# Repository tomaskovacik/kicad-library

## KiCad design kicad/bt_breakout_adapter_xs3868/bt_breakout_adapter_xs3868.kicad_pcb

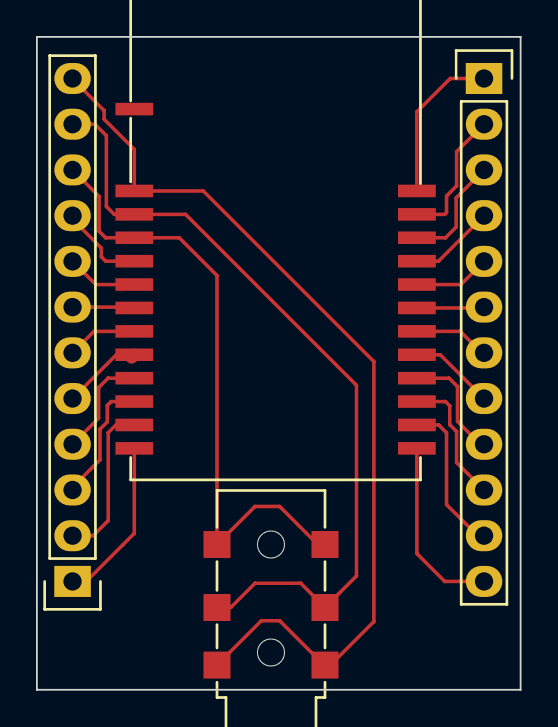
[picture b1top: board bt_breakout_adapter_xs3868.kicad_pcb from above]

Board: 2 copper layers, 26.9 x 36.3 mm, 4 parts (0 on the bottom side), 24 nets.

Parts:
J1: 3.5mm_stereo_jack_PJ242
P1, P2: CONN_01X12; Pin_Header_Straight_1x12
U1: XS3860; XS3868

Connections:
unnamed: J1.1, P1.12, U1.2
unnamed: J1.2, P1.11, U1.3
unnamed: J1.5, P1.10, U1.4
unnamed: P1.1, U1.13
unnamed: P1.2, U1.12
unnamed: P1.3, U1.11
unnamed: P1.4, U1.10
unnamed: P1.5, U1.9
unnamed: P1.6, U1.8
unnamed: P1.7, U1.7
unnamed: P1.8, U1.6
unnamed: P1.9, U1.5
unnamed: P2.1, U1.25
unnamed: P2.2, U1.24
unnamed: P2.3, U1.23
unnamed: P2.4, U1.22
unnamed: P2.5, U1.21
unnamed: P2.6, U1.20
unnamed: P2.7, U1.19
unnamed: P2.8, U1.18
unnamed: P2.9, U1.17
unnamed: P2.10, U1.16
unnamed: P2.11, U1.15
unnamed: P2.12, U1.14

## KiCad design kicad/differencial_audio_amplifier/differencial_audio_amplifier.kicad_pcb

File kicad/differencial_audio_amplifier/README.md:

diferential audio preamplifier for OVC3860 based bluetooth modules, with 0.9V on common audio output, works with blk-md-spk-b, XS3868 and S3860M-S and others.

you can buy boards on tindie:

https://www.tindie.com/products/tomaskovacik/pcb-for-diferential-audio-amplifier/

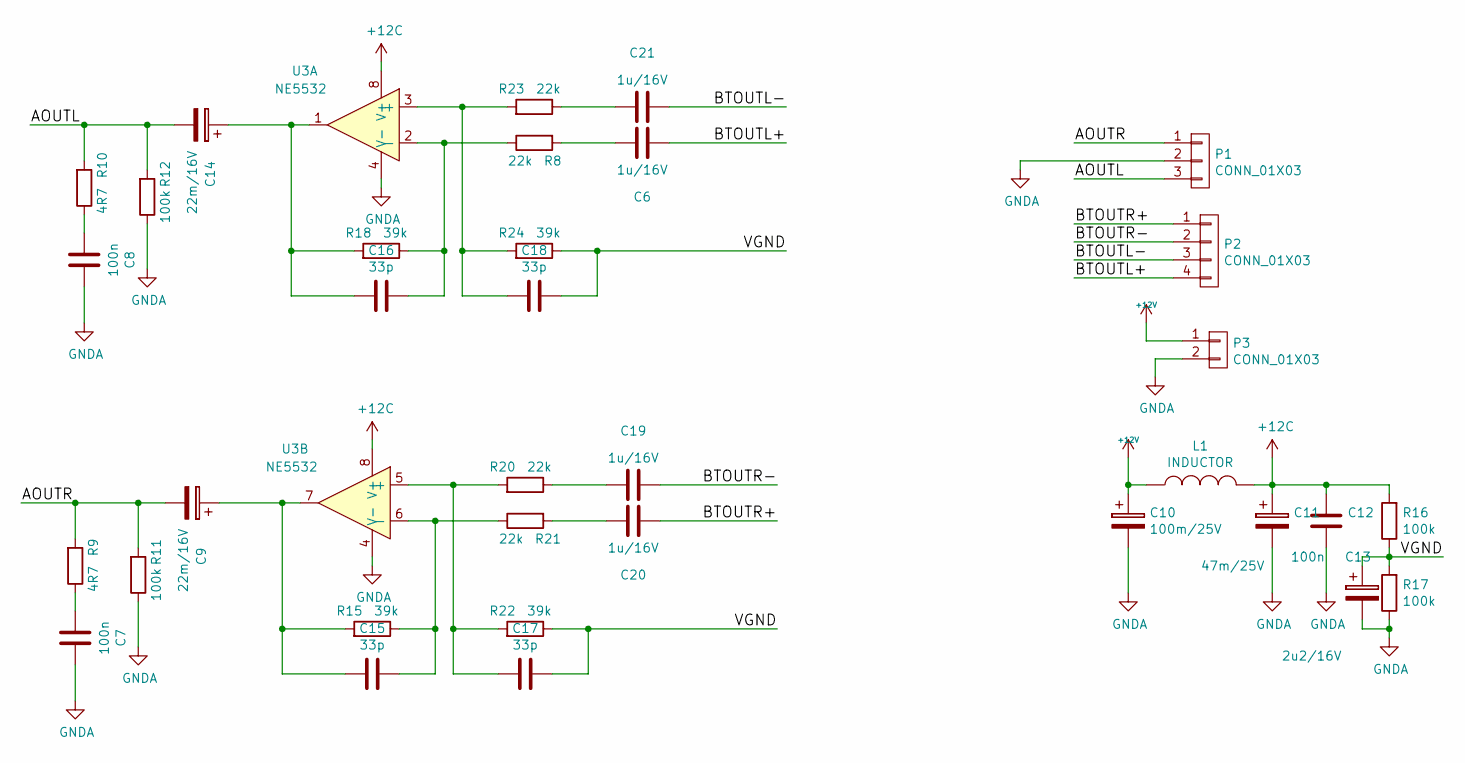
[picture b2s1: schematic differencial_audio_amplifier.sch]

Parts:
C6, C19, C20, C21: 1u/16V; C_0805_HandSoldering
C7, C8, C12: 100n; C_0805_HandSoldering
C9, C14: 22m/16V; c_elec_5x5.3
C10: 100m/25V; c_elec_6.3x7.7
C11: 47m/25V; TantalC_SizeD_EIA-7343_HandSoldering
C13: 2u2/16V; TantalC_SizeA_EIA-3216_HandSoldering
C15, C16, C17, C18: 33p; C_0805_HandSoldering
L1: INDUCTOR; SMD-1210_Pol
P1: CONN_01X03; Pin_Header_Straight_1x03
P2: CONN_01X03; Pin_Header_Straight_1x04
P3: CONN_01X03; Pin_Header_Straight_1x02
R8, R20, R21, R23: 22k; R_0805_HandSoldering
R9, R10: 4R7; R_0805_HandSoldering
R11, R12, R16, R17: 100k; R_0805_HandSoldering
R15, R18, R22, R24: 39k; R_0805_HandSoldering
U3: NE5532; SOIC-8-N

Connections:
+12C: C11.1, C12.1, L1.2, R16.2, U3.8 (V+)
+12V: C10.1, L1.1, P3.1
/AOUTL: C14.2, P1.3, R10.2, R12.2
/AOUTR: C9.2, P1.1, R9.2, R11.2
/BTOUTL+: C6.1, P2.4
/BTOUTL-: C21.2, P2.3
/BTOUTR+: C20.1, P2.1
/BTOUTR-: C19.2, P2.2
/VGND: C13.1, C17.2, C18.2, R16.1, R17.2, R22.1, R24.1
GNDA: C7.2, C8.2, C10.2, C11.2, C12.2, C13.2, P1.2, P3.2, R11.1, R12.1, R17.1, U3.4 (V-)
unnamed: C6.2, R8.2
unnamed: C7.1, R9.1
unnamed: C8.1, R10.1
unnamed: C14.1, C16.1, R18.2, U3.1
unnamed: C9.1, C15.1, R15.2, U3.7
unnamed: C15.2, R15.1, R21.1, U3.6 (-)
unnamed: C16.2, R8.1, R18.1, U3.2 (-)
unnamed: C17.1, R20.2, R22.2, U3.5 (+)
unnamed: C18.1, R23.2, R24.2, U3.3 (+)
unnamed: C19.1, R20.1
unnamed: C20.2, R21.2
unnamed: C21.1, R23.1

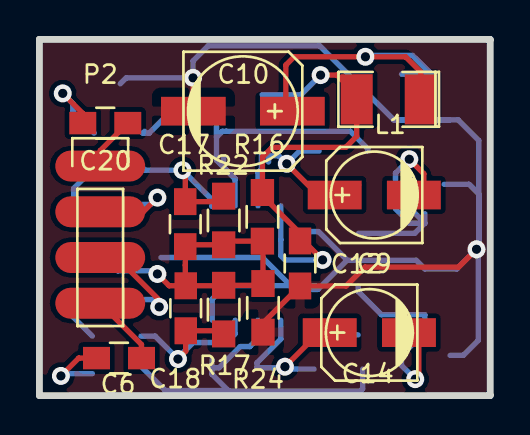
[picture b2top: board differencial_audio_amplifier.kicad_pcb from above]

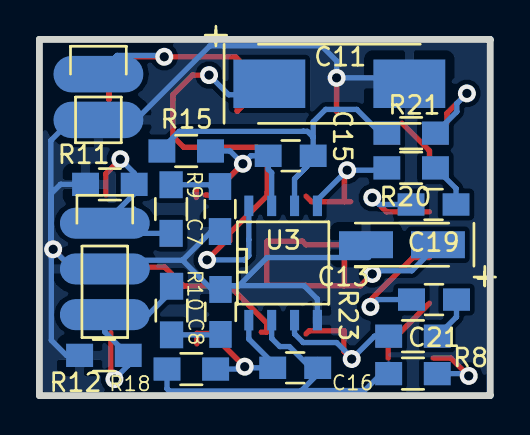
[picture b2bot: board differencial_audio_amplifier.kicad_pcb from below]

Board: 2 copper layers, 25.0 x 19.8 mm, 35 parts (21 on the bottom side), 22 nets.

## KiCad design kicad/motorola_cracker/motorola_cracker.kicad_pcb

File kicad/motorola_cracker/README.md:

for audi chorus1,concert1 cassete radios:

software: http://uloz.to/xmBngiSq/motcrack-v6-exe

to recover password,fix volume problem (yet untested!!!!) simple use dump 4321_no_password.e2p from dumps directory and rewrite MCU eeprom

blog post: http://kovo-blog.blogspot.sk/2015/08/audi-chorus-concert-how-to-recover.html

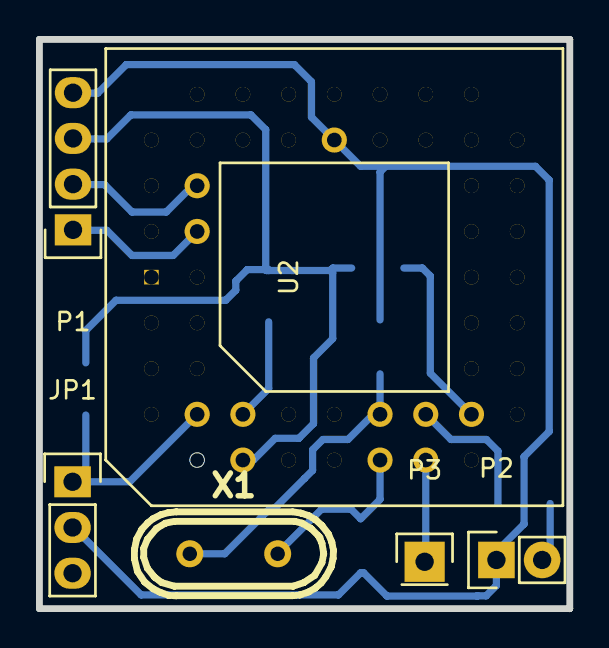
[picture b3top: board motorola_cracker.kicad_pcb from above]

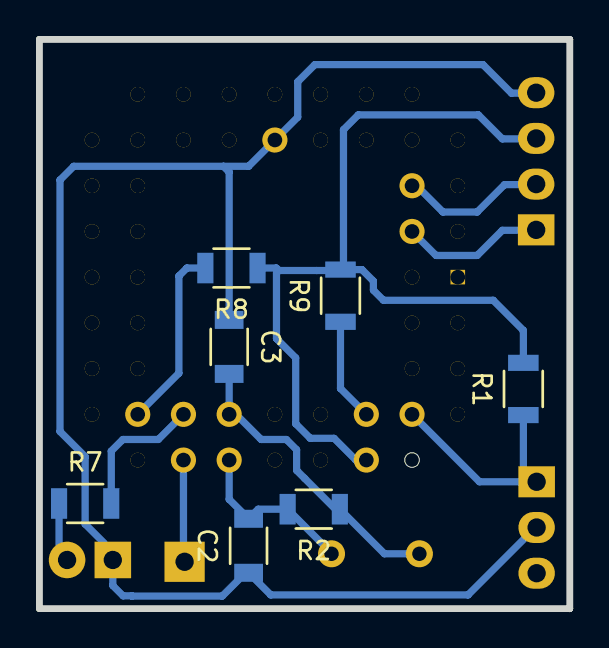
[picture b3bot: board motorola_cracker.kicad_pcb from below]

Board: 2 copper layers, 29.5 x 31.6 mm, 13 parts (7 on the bottom side), 12 nets.

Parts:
C2, C3: 22p; C_1206
JP1: JUMPER3; Pin_Header_Straight_1x03
P1: UART; Pin_Header_Straight_1x04
P2: +12V; Socket_Strip_Straight_1x02
P3: RTS; Pin_Header_Straight_1x01
R1, R7: 10k; R_1206
R2: 100M; R_1206
R8, R9: 1k; R_1206
U2: 68HC05_PLCC; PLCC52
X1: 4Mhz; Crystal_HC49-U_Vertical

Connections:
+5V: P1.3, R1.2, R8.1, R9.2, U2.10
/+12V: P2.2, R7.1
/RESET: P3.1, U2.18
/RX: P1.2, U2.50
/TX: P1.1, U2.52
GND: C2.1, C3.1, JP1.2, P1.4, P2.1, U2.41
unnamed: C2.2, R2.2, U2.16, X1.2
unnamed: C3.2, R2.1, U2.17, X1.1
unnamed: JP1.1, R1.1, U2.9
unnamed: R7.2, U2.19
unnamed: R8.2, U2.22
unnamed: R9.1, U2.11

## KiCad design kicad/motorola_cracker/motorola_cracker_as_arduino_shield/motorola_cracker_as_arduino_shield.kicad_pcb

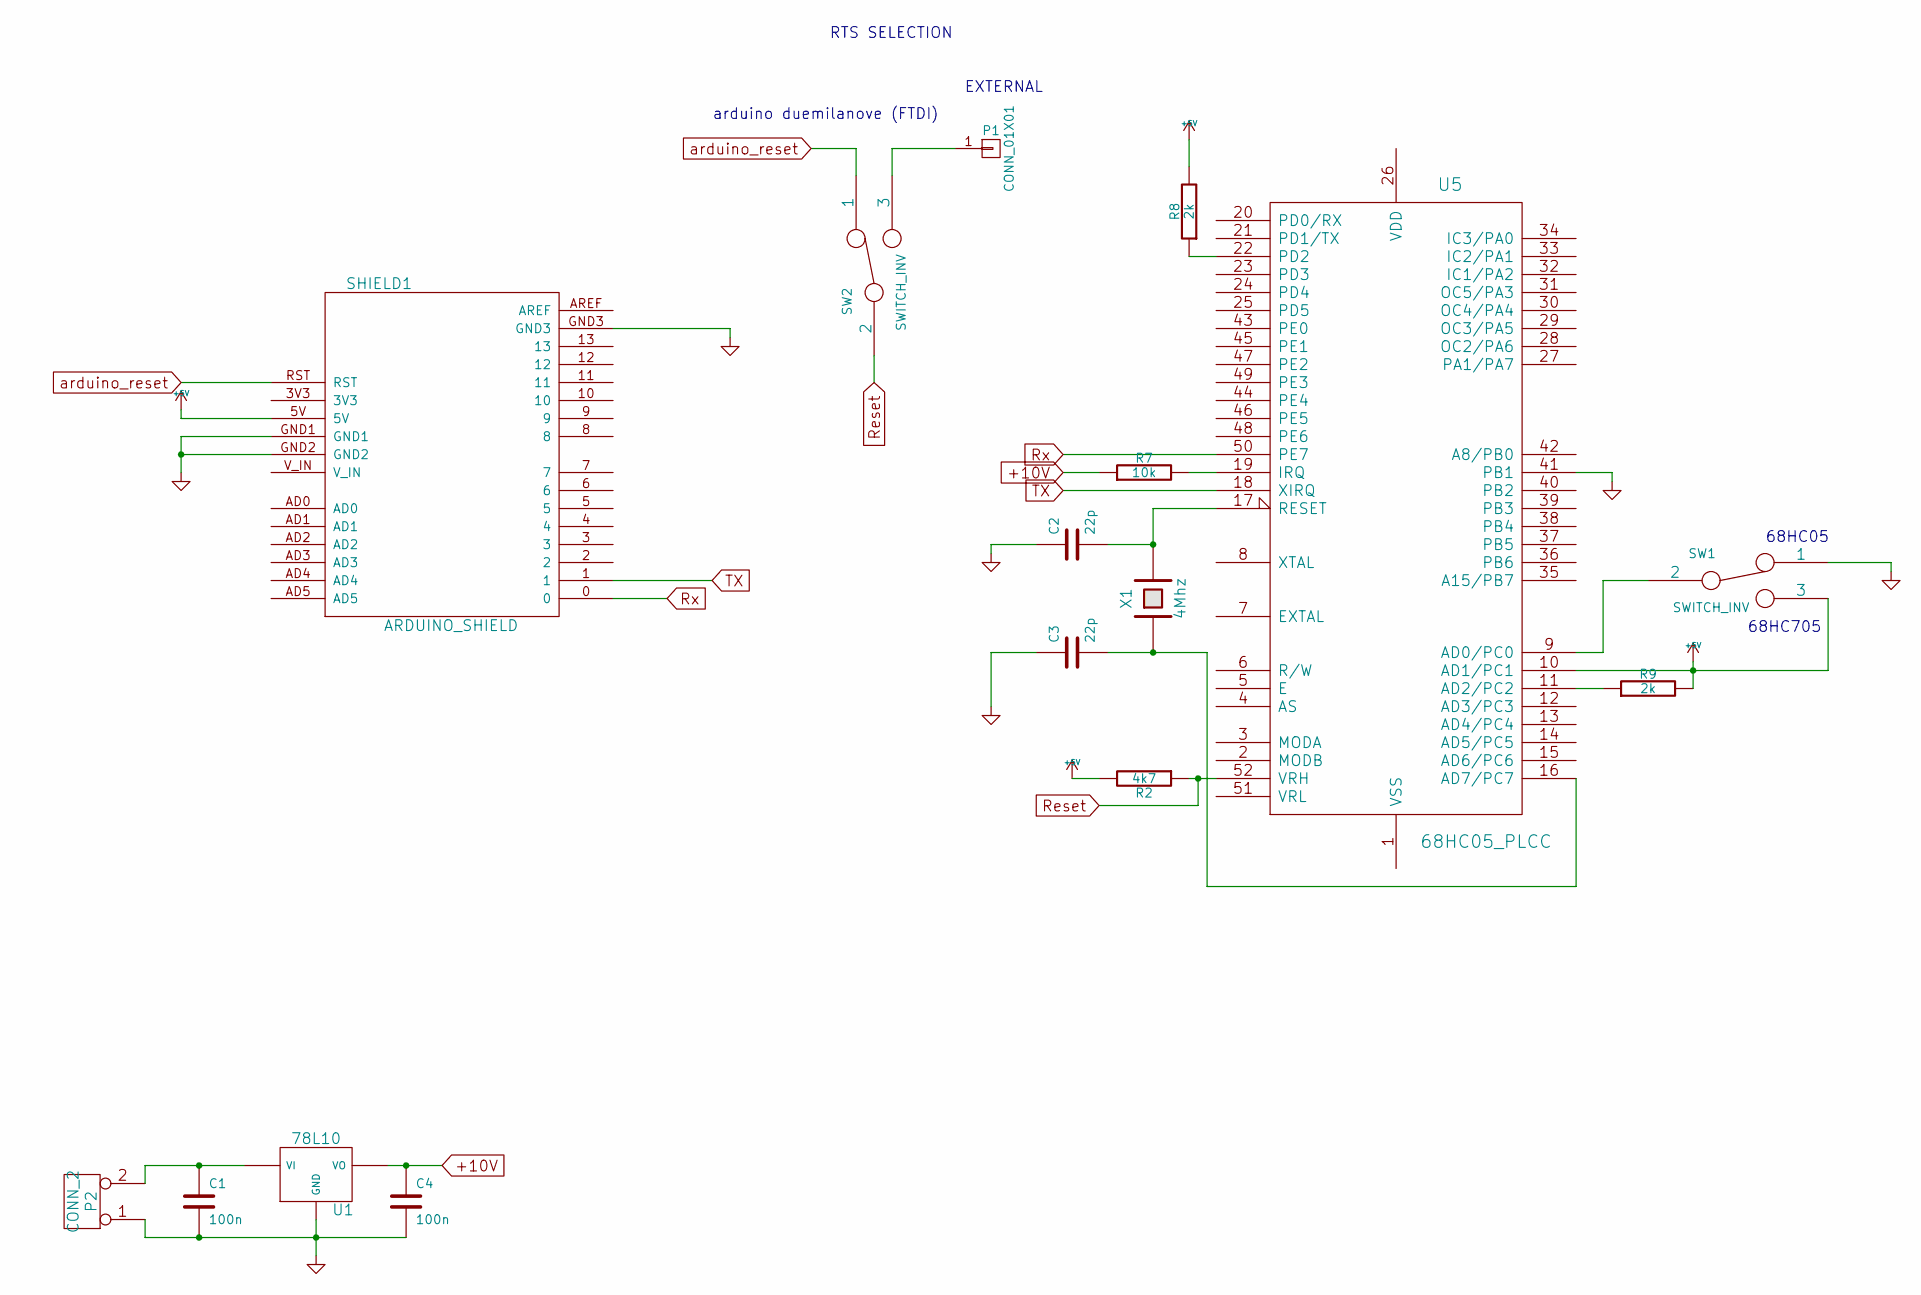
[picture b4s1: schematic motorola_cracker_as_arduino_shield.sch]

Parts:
C1, C4: 100n; Capacitor3MMDiscRM2.5
C2, C3: 22p; Capacitor6MMDiscRM5
P1: CONN_01X01; Socket_Strip_Straight_1x01
P2: CONN_2; AK300-2
R2: 4k7; Resistor_Horizontal_RM10mm
R7: 10k; Resistor_Horizontal_RM10mm
R8, R9: 2k; Resistor_Horizontal_RM10mm
SHIELD1: ARDUINO_SHIELD
SW1, SW2: SWITCH_INV; Pin_Header_Straight_1x03
U1: 78L10; TO92-STABIL
U5: 68HC05_PLCC; PLCC52
X1: 4Mhz; Crystal_HC49-U_Vertical

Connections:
+5V: R2.2, R8.2, R9.2, SHIELD1.5V, SW1.3, U5.10 (AD1/PC1)
+10V: C4.1, R7.1, U1.VO
GND: C1.2, C2.1, C3.1, C4.2, P2.1, SHIELD1.GND1, SHIELD1.GND2, SHIELD1.GND3, SW1.1, U1.GND, U5.41 (PB1)
unnamed: C1.1, P2.2 (PM), U1.VI
unnamed: C2.2, U5.17 (RESET), X1.2
unnamed: C3.2, U5.16 (AD7/PC7), X1.1
unnamed: P1.1, SW2.3
unnamed: R7.2, U5.19 (IRQ)
unnamed: R8.1, U5.22 (PD2)
unnamed: R9.1, U5.11 (AD2/PC2)
unnamed: SW1.2, U5.9 (AD0/PC0)
Reset: R2.1, SW2.2, U5.52 (VRH)
Rx: SHIELD1.0, U5.50 (PE7)
TX: SHIELD1.1, U5.18 (XIRQ)
arduino_reset: SHIELD1.RST, SW2.1

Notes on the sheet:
68HC05
68HC705
EXTERNAL
RTS SELECTION
arduino duemilanove (FTDI)

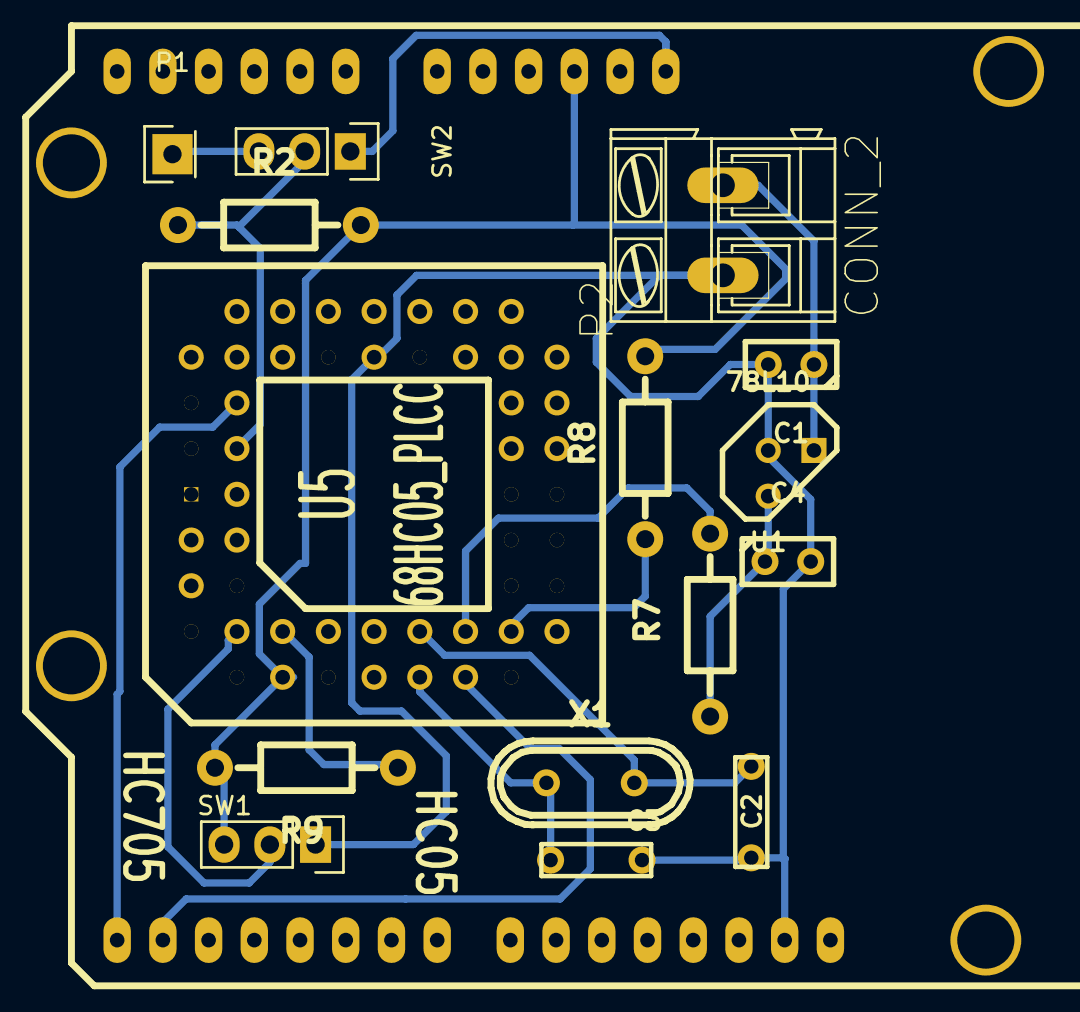
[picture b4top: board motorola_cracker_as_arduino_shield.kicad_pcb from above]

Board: 2 copper layers, 16 parts (0 on the bottom side), 15 nets.

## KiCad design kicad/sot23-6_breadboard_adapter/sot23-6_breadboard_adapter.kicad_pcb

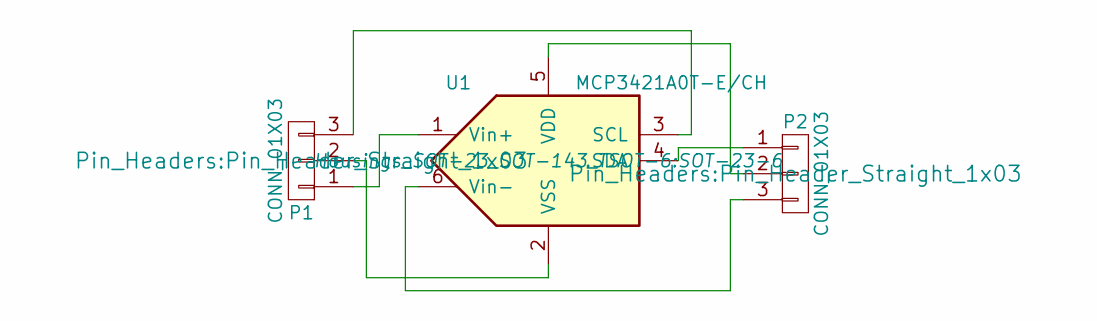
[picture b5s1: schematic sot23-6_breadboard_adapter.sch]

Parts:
P1, P2: CONN_01X03; Pin_Header_Straight_1x03
U1: MCP3421A0T-E/CH; SOT-23-6

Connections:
unnamed: P1.1, U1.1 (Vin+)
unnamed: P1.2, U1.2 (VSS)
unnamed: P1.3, U1.3 (SCL)
unnamed: P2.1, U1.4 (SDA)
unnamed: P2.2, U1.5 (VDD)
unnamed: P2.3, U1.6 (Vin-)

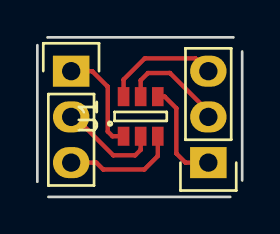
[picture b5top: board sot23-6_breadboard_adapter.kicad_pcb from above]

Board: 2 copper layers, 11.4 x 8.9 mm, 3 parts (0 on the bottom side), 6 nets.

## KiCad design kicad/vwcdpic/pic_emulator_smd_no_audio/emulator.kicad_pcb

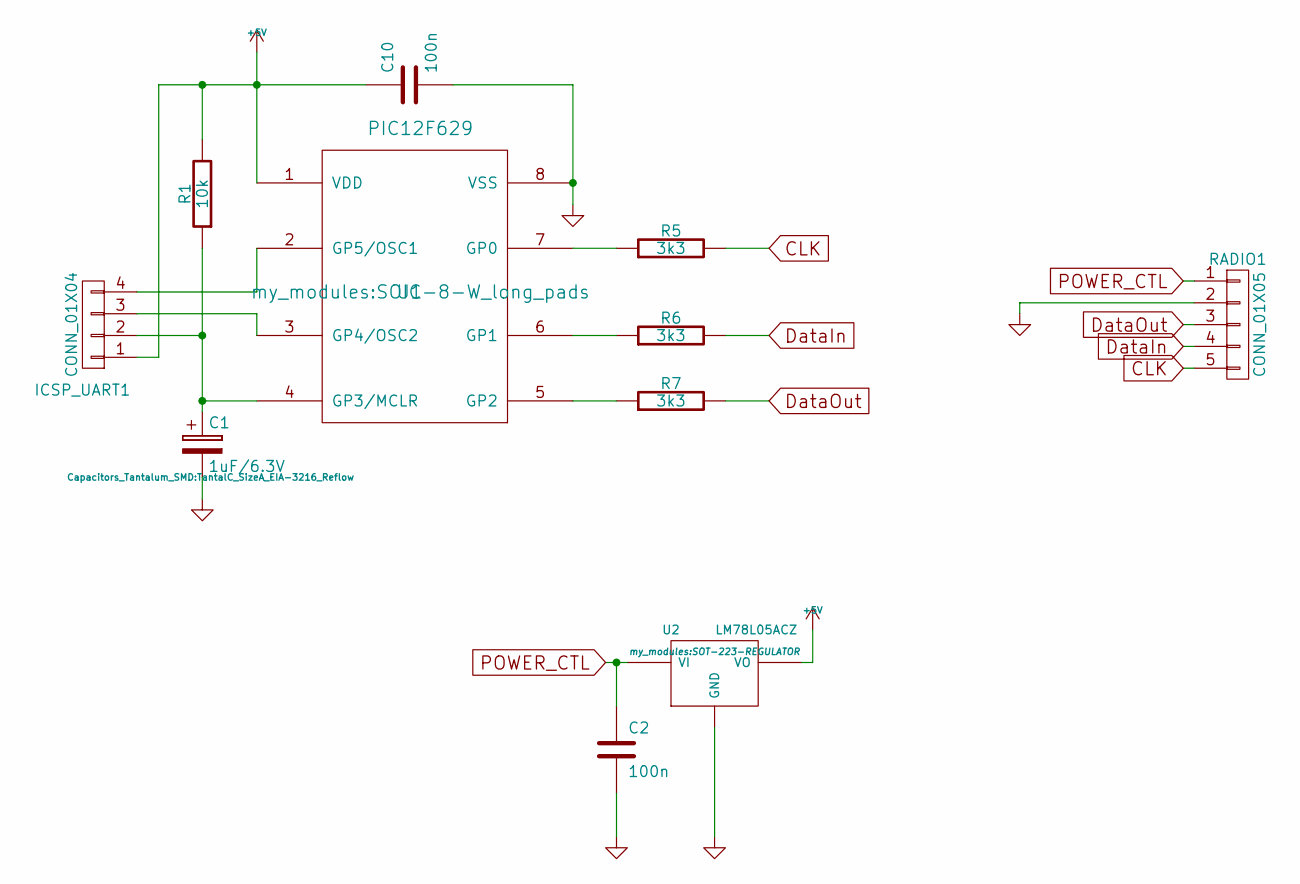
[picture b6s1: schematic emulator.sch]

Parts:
C1: 1uF/6.3V; TantalC_SizeA_EIA-3216_Reflow
C2, C10: 100n; C_0805
ICSP_UART1: CONN_01X04; Pin_Header_Straight_1x04
R1: 10k; R_0805
R5, R6, R7: 3k3; R_0805
RADIO1: CONN_01X05; Pin_Header_Straight_1x05
U1: PIC12F629; SOIC-8-W_long_pads
U2: LM78L05ACZ; SOT-223-REGULATOR

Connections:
+5V: C10.1, ICSP_UART1.1, R1.2, U1.1 (VDD), U2.VO
CLK: R5.2, RADIO1.5
DataIn: R6.2, RADIO1.4
DataOut: R7.2, RADIO1.3
GND: C1.2, C2.2, C10.2, RADIO1.2, U1.8 (VSS), U2.GND
unnamed: C1.1, ICSP_UART1.2, R1.1, U1.4 (GP3/MCLR)
unnamed: ICSP_UART1.3, U1.3 (GP4/OSC2)
unnamed: ICSP_UART1.4, U1.2 (GP5/OSC1)
unnamed: R5.1, U1.7 (GP0)
unnamed: R6.1, U1.6 (GP1)
unnamed: R7.1, U1.5 (GP2)
POWER_CTL: C2.1, RADIO1.1, U2.VI

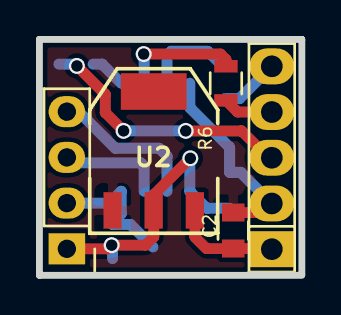
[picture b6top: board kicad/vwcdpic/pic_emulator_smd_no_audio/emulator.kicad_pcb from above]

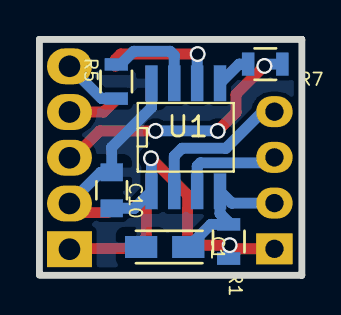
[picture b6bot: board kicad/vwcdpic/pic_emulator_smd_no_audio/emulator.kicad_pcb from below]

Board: 2 copper layers, 14.6 x 13.1 mm, 11 parts (6 on the bottom side), 12 nets.

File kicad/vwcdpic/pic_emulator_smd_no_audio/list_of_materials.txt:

C1	 - 1uF/6.3V, Tantal Size A
C10,2    - 100n, 1206
R1       - 10k,  1206
R5,6,7   - 3k3,  1206
U1       - PIC12F629-I/SN, SW: VWCPIC v2 or v3, 8SOIC
U2       - AMS-1117-5.0 (5V) SOT-223

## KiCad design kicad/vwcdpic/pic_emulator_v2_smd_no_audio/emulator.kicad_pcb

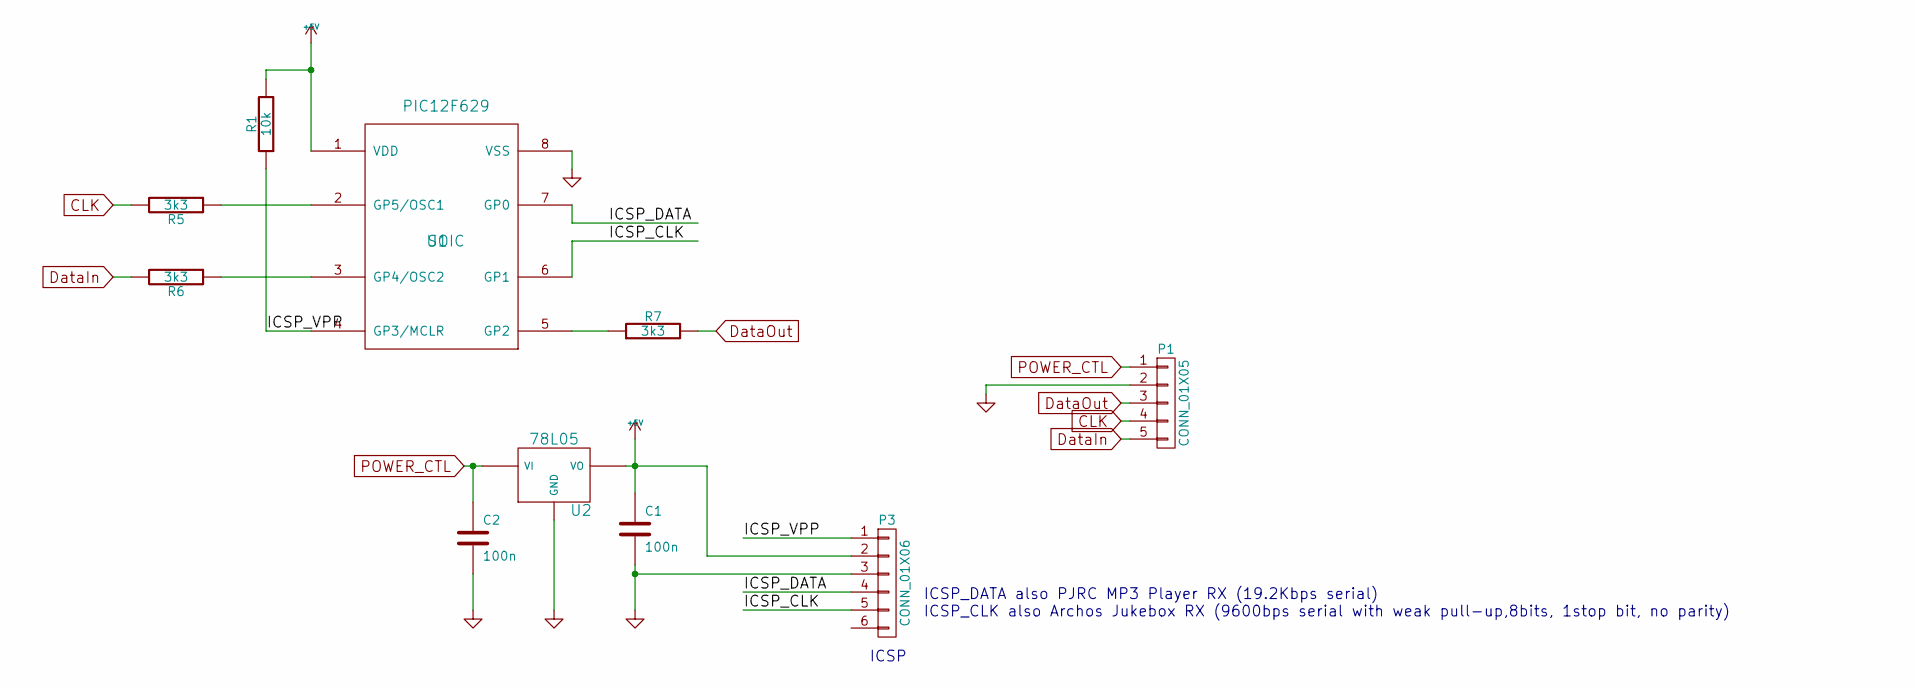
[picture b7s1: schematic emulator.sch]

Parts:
C1, C2: 100n
P1: CONN_01X05
P3: CONN_01X06
R1: 10k
R5, R6, R7: 3k3
U1: PIC12F629; SOIC
U2: 78L05

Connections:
+5V: C1.1, P3.2, R1.2, U1.1 (VDD), U2.VO
/ICSP_CLK: P3.5, U1.6 (GP1)
/ICSP_DATA: P3.4, U1.7 (GP0)
/ICSP_VPP: P3.1, R1.1, U1.4 (GP3/MCLR)
CLK: P1.4, R5.2
DataIn: P1.5, R6.2
DataOut: P1.3, R7.2
GND: C1.2, C2.2, P1.2, P3.3, U1.8 (VSS), U2.GND
unnamed: R5.1, U1.2 (GP5/OSC1)
unnamed: R6.1, U1.3 (GP4/OSC2)
unnamed: R7.1, U1.5 (GP2)
POWER_CTL: C2.1, P1.1, U2.VI

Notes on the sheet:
ICSP_DATA also PJRC MP3 Player RX (19.2Kbps serial) ICSP_CLK also Archos Jukebox RX (9600bps serial with weak pull-up,8bits, 1stop bit, no parity)
ICSP

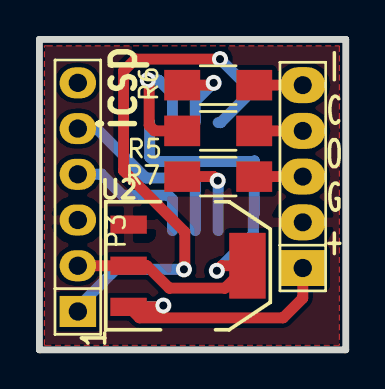
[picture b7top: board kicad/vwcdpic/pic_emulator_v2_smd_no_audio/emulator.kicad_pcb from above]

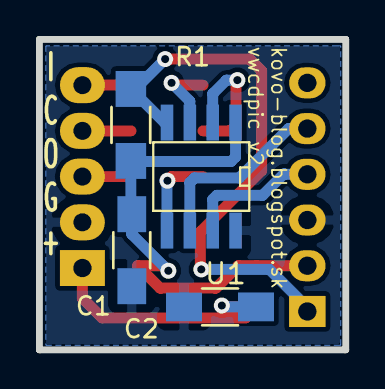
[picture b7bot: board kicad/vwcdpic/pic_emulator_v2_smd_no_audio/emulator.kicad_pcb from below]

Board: 2 copper layers, 17.0 x 17.2 mm, 10 parts (4 on the bottom side), 12 nets.
